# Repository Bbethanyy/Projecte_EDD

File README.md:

View this project on [CADLAB.io](https://cadlab.io/project/26669). 

# Projecte EDD: Disseny eletrònic d'un maleter
**Membres del grup:** Jan Castillo, Bethany Quintero
----------------------------------------------------
## Objectiu
Dissenyar un sistema electrònic capaç d'obrir un maleter d'un automòbil utilitzant un sensor de proximitat i que pogui escalfar el vidre que l'acompanya.

## Requisits/Especificacions
- Microcontrolador 
- Dos reguladors de tensions: un pel microcontrolador i l'altre per al sensor
- Sensor de proximitat per detectar un gest amb el peu 
- Resistèncias calefactores per escalar el vidre
- Driver per controlar el Brushless DC motor per obrir i tancar el maleter
- Resistor shunt per indicar el final de la carerra
- Connectors

## Diagrama de blocs

## Components
| Ref. | Descripció| Datasheet |
| ------ | -----------------| ------------------|
|PIC18F258|Microcontrolador|[Datasheet](https://www.mouser.es/datasheet/2/268/41159e-30206.pdf)|
|LM1117|Regulador de tensió|[Datasheet](https://www.ti.com/lit/ds/snos412q/snos412q.pdf?ts=1679503528555&ref_url=https%253A%252F%252Fwww.ti.com%252F)|
|FDC2212|Sensor de proximitat|[Datasheet](https://www.ti.com/lit/ds/symlink/fdc2212-q1.pdf?ts=1679569328592&ref_url=https%253A%252F%252Fwww.ti.com%252Fproduct%252FFDC2212-Q1)|
|MCP2551|Transceiver|[Datasheet](https://www.mouser.es/datasheet/2/268/20001667G-1115479.pdf)|
|ECS-80-20-20A-TR|Oscillador|[Datasheet](https://ecsxtal.com/store/pdf/csm-8r.pdf)|
|PSR100|Shunt resistor|[Datasheet](https://fscdn.rohm.com/en/products/databook/datasheet/passive/resistor/chip_resistor/psr-e.pdf)|
|AD8616|OpAmp|[Datasheet](https://www.analog.com/media/en/technical-documentation/data-sheets/AD8615_8616_8618.pdf)|
|ADW1112W|Relé|[Datasheet](https://www.datasheetq.com/datasheet-download/853198/1/Panasonic/ADW1112W)|
|1393280-5|Relé micro K|[Datasheet](https://www.te.com/commerce/DocumentDelivery/DDEController?Action=srchrtrv&DocNm=V23086X0000A001&DocType=Data+Sheet&DocLang=English&DocFormat=pdf&PartCntxt=1393280-5)|
|BLDC-48|Brushless motor|[Datasheet](https://www.farnell.com/datasheets/526541.pdf)|
|GBR-612|Heating Element|[Datasheet](https://www.tme.eu/Document/745dece1e8a1927996aa7af3a5cfc3a0/GBR-612_ENG.pdf)|
|BC 817/25|BJT|[Datasheet](https://pdf1.alldatasheet.com/datasheet-pdf/view/16111/PHILIPS/BC817-25.html)|
|TCA39306|Level Shifter|[Datasheet](https://www.ti.com/lit/ds/symlink/tca39306.pdf?ts=1680614676613&ref_url=https%253A%252F%252Fwww.google.com%252F)|

## Simulacions
Anem a veure diferents simulacions que hem pogut fer amb LTSPICE per comprovar el correcte funcionament del projecte.
### Reguladors de tensió
El primer a simular ha estat els reguladors de tensió a utilitzar, una de les més senzilles:

I podem comprovar que els potencials als nodes són els dessitjats:

### Relé
Malauradament LTSPICE no té relés. Hem utilitzat un interruptor per tensió i hem aproximat alguns dels seus paràmetres al nostre relé, per a fer una simulació aproximada:

I així, podem comprovar que passa la tensió dessitjada:

### Control de corrent
L'últim sistema que podem simular és el sistema d'amplificadors operacionals que permetran regular el corrent del motor i, per tant, el final de carrera d'aquest:

Aleshores es pot comprovar que si la font és de 1.33 A (funcionament normal), la sortida és el valor baix de saturació:

I en canvi, si la font és de 1.95 A (realment es retallaria abans), la sortida serà el valor alt de tensió:

## Esquemàtic

## Layout

## 3D Model

## Costos finals:
|Cantitat de PCBs| Preu |Stencil|
| ------ | -----------------| ------------------|
|10|562,668 €|No|
|50|2520,3 €|Sí|
|1000|36316,84 €|Sí|
|20000|709205,21 €|Sí|

## Historial de canvis
|Data| Autor/a |Descripció|
| ------ | -----------------| ------------------|
|23/03/23|Bethany Quintero i Jan Castillo|Segona versió diagrama de blocs i selecció de components|
|23/03/23|Bethany Quintero i Jan Castillo|Correcció diagrama de blocs i afegit el BJT a components|
|26/03/23|Jan Castillo|Actualització diagrama de blocs i components (OPAMP). Afegides les simulacions i els resultats|
|27/03/23|Jan Castillo|Actualització de components (driver canviat per relés) i, per tant, actualitzat també el diagrama de blocs. Actualització de la simulació del final de carrera|
|27/03/23| Bethany Quintero | Primera versió de l'esquemàtic|
|28/03/23| Bethany Quintero | Correcció del driver i afegits els valors dels components que faltaven a l'esquemàtic|
|1/04/23| Jan Castillo |Afegit Level Shifter a components. Actualització del diagrama de blocs i canviat el valor Vref de la simulació del final de carrera.|
|2/04/23| Jan Castillo |Canviat Level Shifter i, per tant, el diagrama de blocs.|
|5/04/23| Bethany Quintero | Canviat el model del level shifter. Actualització esquemàtic: afegits els divisors de tensions per Vref i level shifter.|
|6/04/23| Jan Castillo | Alguns canvis a l'esquemàtic.|
|6/04/23| Bethany Quintero | Canvi a l'esquemàtic.|
|9/04/23| Bethany Quintero | Canvi de nets a l'esquemàti.c|
|10/04/23| Jan Castillo i Bethany Quintero |Primera versió Layout.|
|23/04/23| Jan Castillo i Bethany Quintero |Actualització diagrama de blocs, esquemàtic i layout finals.|
|25/04/23| Jan Castillo i Bethany Quintero |Afegit de pressupostos i petits canvis al layout.|

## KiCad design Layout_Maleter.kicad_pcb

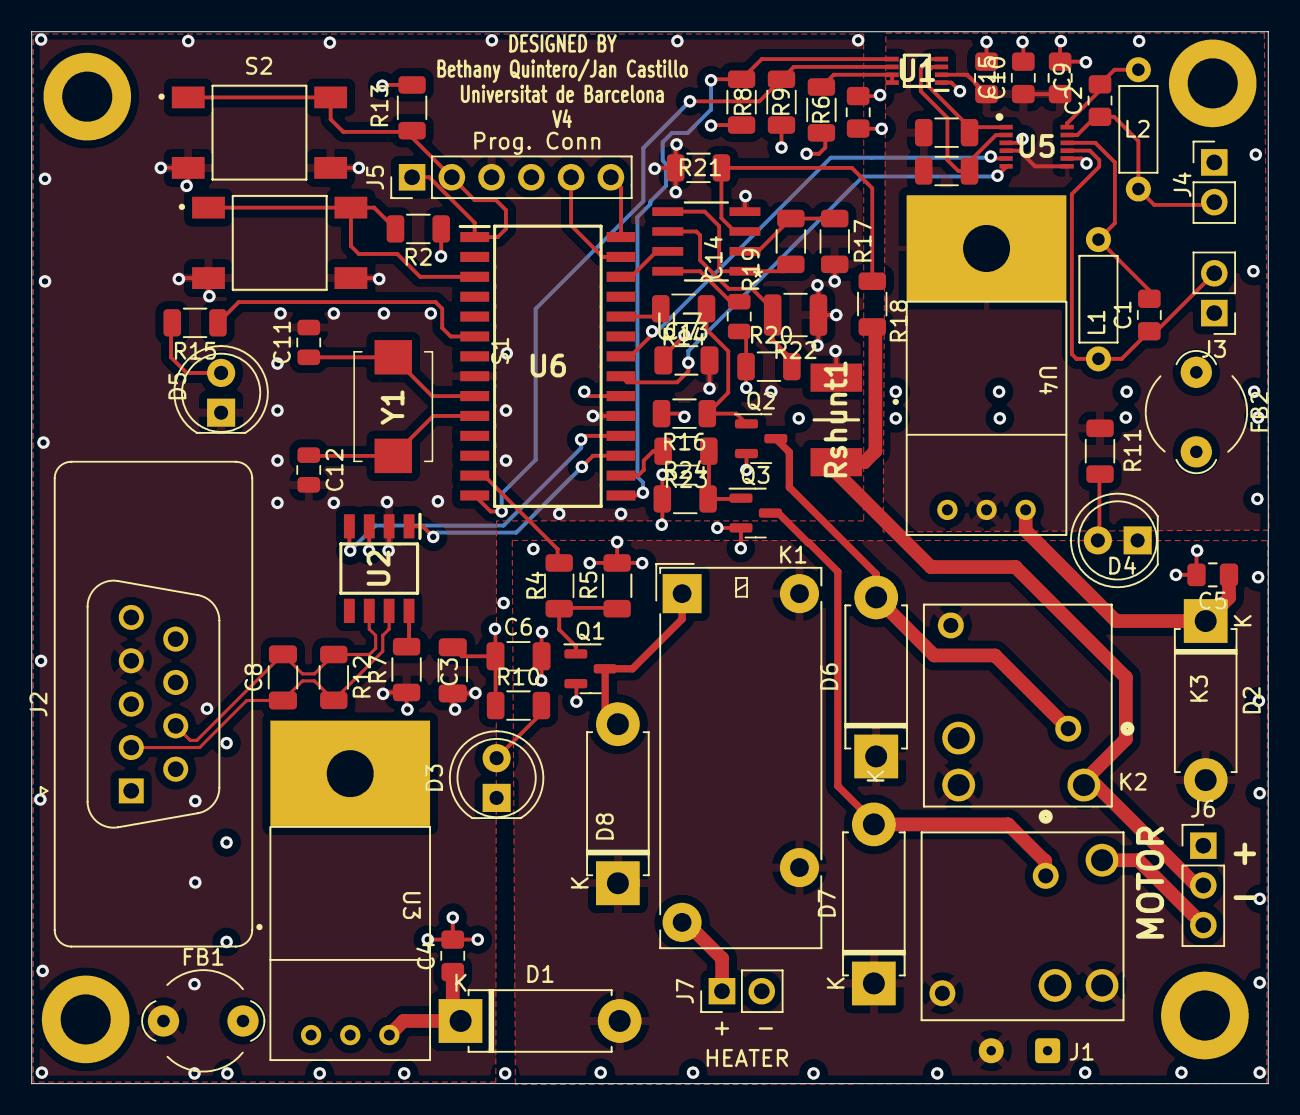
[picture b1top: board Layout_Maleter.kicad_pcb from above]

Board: 4 copper layers, 79.0 x 67.2 mm, 75 parts (0 on the bottom side), 51 nets.

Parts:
C1, C2: 33pF; C_0805_2012Metric_Pad1.18x1.45mm_HandSolder
C3, C13: 100nF; C_1206_3216Metric
C4, C5: 10uF; C_0805_2012Metric_Pad1.18x1.45mm_HandSolder
C6: 10uF; C_1206_3216Metric
C8: 100pF; C_1206_3216Metric
C9, C15, C16: 0.1 uF; C_0805_2012Metric_Pad1.18x1.45mm_HandSolder
C10: 0.1uF; C_0805_2012Metric_Pad1.18x1.45mm_HandSolder
C11, C12: 15 pF; C_0805_2012Metric
C14: 100 nF; C_0805_2012Metric
D1, D2, D6, D7, D8: 1N4002; D_5W_P10.16mm_Horizontal
D3, D4, D5: LED; LED_D5.0mm
FB1, FB2: FerriteBead_Small; LairdTech_28C0236-0JW-10
J1: Conn_01x02; SolderWire-0.1sqmm_1x02_P3.6mm_D0.4mm_OD1mm
J2: DB9_Male; DSUB-9_Male_Vertical_P2.77x2.84mm
J3, J4, J7: Conn_01x02; PinHeader_1x02_P2.54mm_Vertical
J5: Conn_01x06_Fem; PinHeader_1x06_P2.54mm_Vertical
J6: Conn_Male; PinHeader_1x03_P2.54mm_Vertical
K1: ADW11; Relay_1P1T_NO_10x24x18.8mm_Panasonic_ADW11xxxxW_THT
K2, K3: 1393280-5; RELAY_1393280-5
L1, L2: 18uH; L_Axial_L5.3mm_D2.2mm_P7.62mm_Horizontal_Vishay_IM-1
Q1, Q2, Q3: BC817; SOT-23
R1, R3, R8, R9: 22k; R_1206_3216Metric
R2, R13: 10K; R_1206_3216Metric
R4, R14, R23: 60k; R_1206_3216Metric
R5, R16, R20, R24: 10k; R_1206_3216Metric
R6: 200k; R_1206_3216Metric
R7: 20k; R_1206_3216Metric
R10, R11, R15, R17, R18: 1k; R_1206_3216Metric
R12: 60; R_1206_3216Metric
R19, R21: 100k; R_1206_3216Metric
R22: 120k; R_1210_3225Metric
Rshunt1: 2m; ShuntRes
S1, S2: 2-1437565-7; SW_2-1437565-7
U1: TCA39306DTMR; SOP50P310X90-8N
U2: MCP2551-I-P; TRANSCEIVER_SMD
U3: LM1117-5.0; TO-220
U4: LM1117-3.3; TO-220
U5: FDC2212QDNTTQ1; SON50P400X400X100-13N
U6: PIC18F258-I/SP; MICROSMD
U7: AD8616ARZ; SOIC127P600X175-8N
Y1: Crystal; CRISTALL

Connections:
+VCC1: C3.1, C6.1, C13.1, C14.1, C16.1, J5.4, R2.1, R6.1, R8.1, R9.1, R10.1, R13.1, R20.1, U2.3 (VDD), U3.2 (VO), U3.4, U6.20 (VDD)
+VCC2: C9.1, C10.1, C15.1, R1.1, R3.1, R11.1, U1.2 (VREF1), U4.2 (VO), U4.4, U5.4 (ADDR), U5.7 (VDD)
/CAN+: C8.1, J2.2, R12.2, U2.7 (CANH)
/CAN-: C8.2, J2.7, R12.1, U2.6 (CANL)
/Heater: R2.2, S1.1, S1.2, U6.3 (RA1/AN1)
/INTB: U5.5 (INTB), U6.22 (RB1/INT1)
/IN_B: R19.2, U7.1 (OUT_A), U7.5 (+INB)
/OSC1: C11.1, U6.9 (OSC1/CLKI), Y1.1
/OSC2: C12.1, U6.10 (OSC2/CLKO/RA6), Y1.2
/PGC: J5.5, U6.27 (RB6/PGC)
/PGD: J5.6, U6.28 (RB7/PGD)
/PMW_5V: R4.2, U6.13 (RC2/CCP1)
/RESET: J5.1, J5.2, R13.2, S2.1, S2.2, U6.1 (~MCLR/VPP)
/RX_CAN: U2.4 (RXD), U6.18 (RC7/RX/DT)
/Relé1: R14.2, U6.24 (RB3/CANRX)
/Relé2: R23.2, U6.16 (RC5/SDO)
/SCL1: R1.2, U1.3 (SCL1), U5.1 (SCL)
/SCL2: R9.2, U1.6 (SCL2), U6.14 (RC3/SCK/SCL)
/SD: U5.6 (SD), U6.21 (RB0/INT0)
/SDA1: R3.2, U1.4 (SDA1), U5.2 (SDA)
/SDA2: R8.2, U1.5 (SDA2), U6.15 (RC4/SDI/SDA)
/TX_CAN: U2.1 (TXD), U6.17 (RC6/TX/CK)
GND: C3.2, C9.2, C10.2, C11.2, C12.2, C13.2, C15.2, C16.2, D5.1 (K), FB1.1, FB2.1, J1.1, J2.4, J3.1, J4.1, J5.3, R7.1, R17.2, R21.1, R22.1, Rshunt1.2, S1.3, S1.4, S2.3, S2.4, U1.1 (GND), U2.2 (VSS), U5.3 (CLKIN), U5.8 (GND), U6.8 (VSS), U6.19 (VSS), U7.4 (V-)
GNDPWR: C4.2, C5.2, C6.2, D3.1 (K), D4.1 (K), FB1.2, FB2.2, J6.1, J7.2, K2.5, K3.5, Q1.2 (E), Q2.2 (E), Q3.2 (E), R5.2, R16.2, R24.1, U3.1 (GND), U4.1 (GND)
INTERRP: U6.26 (RB5/PGM), U7.7 (OUT_B)
M1: J6.2, K2.4, R18.2, Rshunt1.1
M2: J6.3, K3.4
unnamed: C1.1, J3.2, L1.1, U5.9 (IN0A)
unnamed: C1.2, L1.2, U5.10 (IN0B)
unnamed: C2.1, J4.2, L2.1, U5.11 (IN1A)
unnamed: C2.2, L2.2, U5.12 (IN1B)
unnamed: C4.1, D1.1 (K), U3.3 (VI)
unnamed: C5.1, D2.1 (K), U4.3 (VI)
unnamed: C14.2, U7.8 (V+)
unnamed: D3.2 (A), R10.2
unnamed: D4.2 (A), R11.2
unnamed: D5.2 (A), R15.2
unnamed: D6.2 (A), K2.1, Q2.3 (C)
unnamed: D7.2 (A), K3.1, Q3.3 (C)
unnamed: D8.2 (A), K1.1, Q1.3 (C)
unnamed: J7.1, K1.3
unnamed: Q1.1 (B), R4.1, R5.1
unnamed: Q2.1 (B), R14.1, R16.1
unnamed: Q3.1 (B), R23.1, R24.2
unnamed: R6.2, U1.7 (VREF2), U1.8 (EN)
unnamed: R7.2, U2.8 (Rs)
unnamed: R15.1, U6.6 (RA4/T0CKI)
unnamed: R17.1, R19.1, U7.2 (-INA)
unnamed: R18.1, R21.2, U7.3 (+INA)
unnamed: R20.2, R22.2, U7.6 (-INB)
VBAT: D1.2 (A), D2.2 (A), D6.1 (K), D7.1 (K), D8.1 (K), J1.2, K1.5, K1.6, K2.2, K2.3, K3.2, K3.3

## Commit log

2023-03-23 Backlink to CADLAB.io has been added.
